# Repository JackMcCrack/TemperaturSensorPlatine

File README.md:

TemperaturSensorPlatine
=======================

Dallas 1wire bus sensors

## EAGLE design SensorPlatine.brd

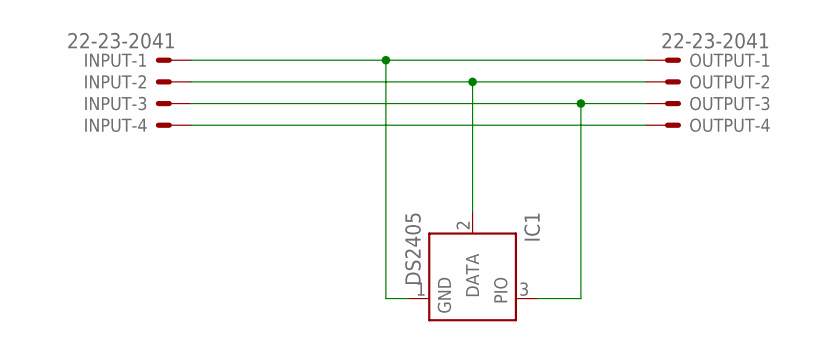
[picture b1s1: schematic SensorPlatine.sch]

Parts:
IC1: DS2405; TO92-
INPUT: 22-23-2041
OUTPUT: 22-23-2041

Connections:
DATA: IC1.2 (DATA), INPUT.2, OUTPUT.2
GND: IC1.1 (GND), INPUT.1, OUTPUT.1
unnamed: IC1.3 (PIO), INPUT.3, OUTPUT.3
RESERVED: INPUT.4, OUTPUT.4

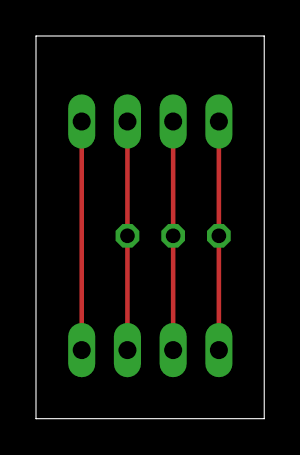
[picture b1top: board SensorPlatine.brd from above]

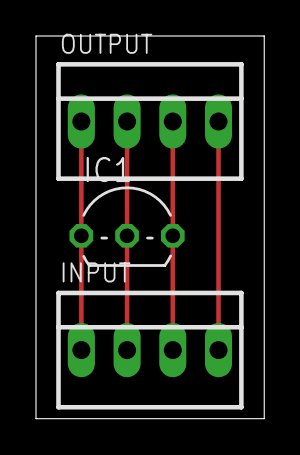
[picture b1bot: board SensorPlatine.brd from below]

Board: 2 copper layers, 12.7 x 21.3 mm, 3 parts (3 on the bottom side), 4 nets.

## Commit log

2014-10-29 Sensorplatine Version1
